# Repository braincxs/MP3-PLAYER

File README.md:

hello, I am Brian (16 years old)

During exam, i keep seeing people using a EXPENSIVE mp3 player around RM200 (50$), and it's not even hard to build so I said why not build one and that's what i did :)
And it was a lot of fun, pcb designing is a MUST TRY

# BITSTREAM
This is a compact pcb for a custom mp3 player
## Features
- A 8Ω, 2W speaker
- A audio jack for wired earphones
- A tft display screen
- a dfplayer mini and a micro sd car to upload your music
- 4 buttons to select your music
- a rotary encoder to adjust the volume
- an arduino nano

## HOW THIS WAS MADE
I used kicad to make this and it was my first time doing so i think it will have some problem but idk :p

## AI DISCLOSURE
I did use some ai to ask about the safety of the project like what type of battery to use and should i add more resistor.

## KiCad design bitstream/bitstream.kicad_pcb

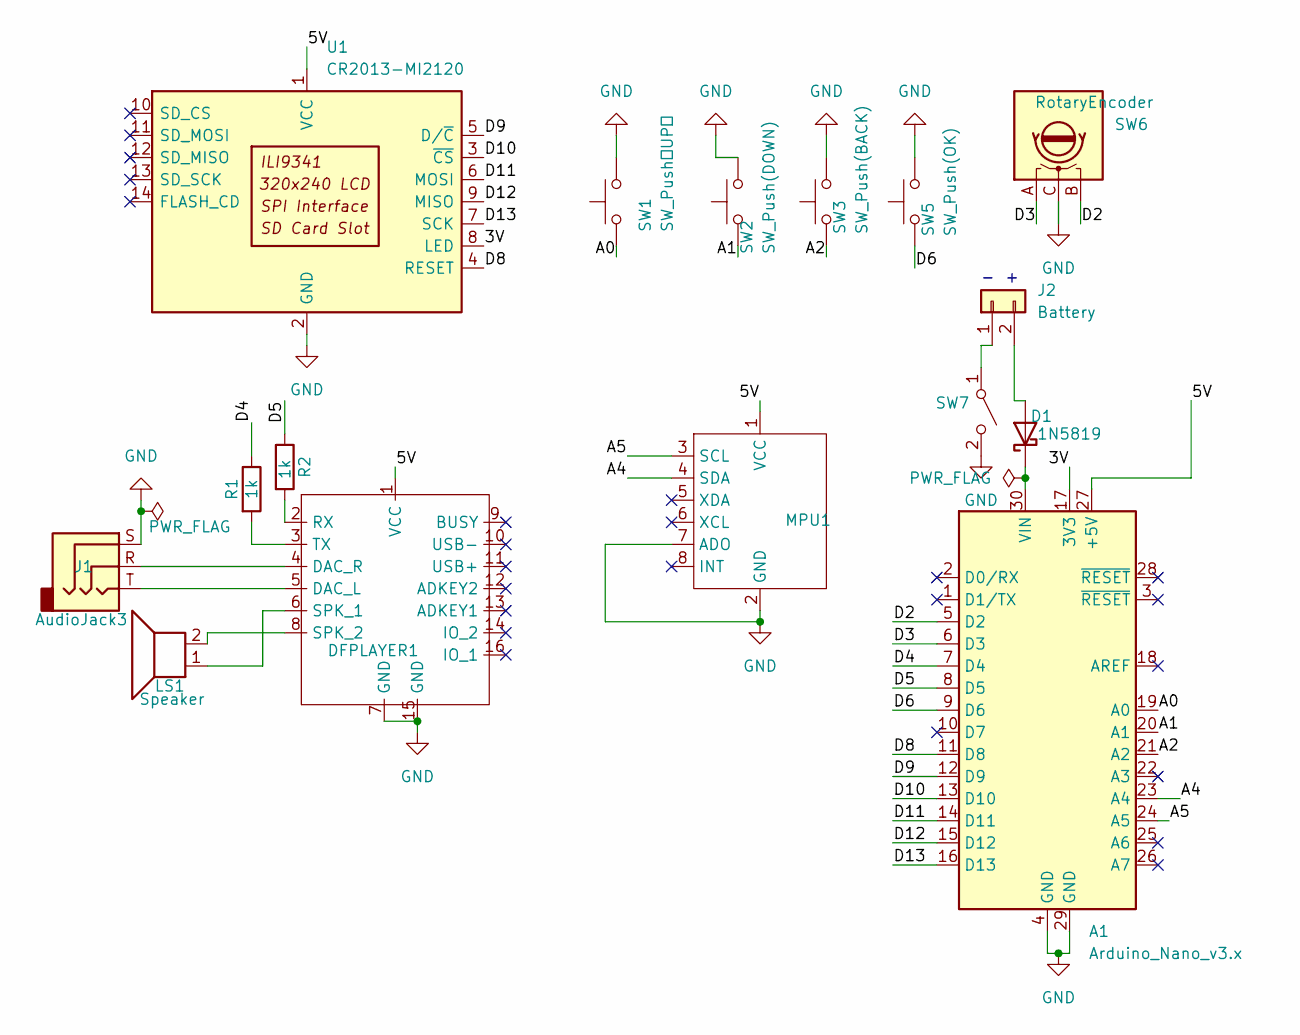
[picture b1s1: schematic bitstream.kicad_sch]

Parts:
A1: Arduino_Nano_v3.x; Arduino_Nano
D1: 1N5819; D_DO-41_SOD81_P10.16mm_Horizontal
DFPLAYER1: dfplayer
J1: AudioJack3; Jack_3.5mm_CUI_SJ-3523-SMT_Horizontal
J2: Battery; TerminalBlock_MaiXu_MX126-5.0-02P_1x02_P5.00mm
LS1: Speaker; SolderWire-0.75sqmm_1x02_P7mm_D1.25mm_OD3.5mm
MPU1: mpu6050
R1, R2: 1k; R_1210_3225Metric_Pad1.30x2.65mm_HandSolder
SW1: SW_Push（UP）; SW_Cherry_MX_1.25u_PCB
SW2: SW_Push(DOWN); SW_Cherry_MX_1.25u_PCB
SW3: SW_Push(BACK); SW_Cherry_MX_1.25u_PCB
SW5: SW_Push(OK); SW_Cherry_MX_1.25u_PCB
SW6: RotaryEncoder; RotaryEncoder_Alps_EC11E-Switch_Vertical_H20mm
SW7: Power switch; SW_Slide_SPDT_Angled_CK_OS102011MA1Q
U1: CR2013-MI2120

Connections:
/3V: A1.17 (3V3), U1.8 (LED)
/5V: A1.27 (+5V), DFPLAYER1.1 (VCC), MPU1.1 (VCC), U1.1 (VCC)
/A0: A1.19 (A0), SW1.1
/A1: A1.20 (A1), SW2.1
/A2: A1.21 (A2), SW3.1
/A4: A1.23 (A4), MPU1.4 (SDA)
/A5: A1.24 (A5), MPU1.3 (SCL)
/D2: A1.5 (D2), SW6.B
/D3: A1.6 (D3), SW6.A
/D4: A1.7 (D4), R1.1
/D5: A1.8 (D5), R2.1
/D6: A1.9 (D6), SW5.1
/D8: A1.11 (D8), U1.4 (RESET)
/D9: A1.12 (D9), U1.5 (D/~C)
/D10: A1.13 (D10), U1.3 (~CS)
/D11: A1.14 (D11), U1.6 (MOSI)
/D12: A1.15 (D12), U1.9 (MISO)
/D13: A1.16 (D13), U1.7 (SCK)
GND: A1.4 (GND), A1.29 (GND), DFPLAYER1.7 (GND), DFPLAYER1.15 (GND), J1.S, MPU1.2 (GND), MPU1.7 (ADO), SW1.2, SW2.2, SW3.2, SW5.2, SW6.C, SW7.2 (B), U1.2 (GND)
unnamed: A1.30 (VIN), D1.1 (K)
unnamed: D1.2 (A), J2.2
unnamed: DFPLAYER1.5 (DAC_L), J1.T
unnamed: DFPLAYER1.4 (DAC_R), J1.R
unnamed: DFPLAYER1.2 (RX), R2.2
unnamed: DFPLAYER1.6 (SPK_1), LS1.1
unnamed: DFPLAYER1.8 (SPK_2), LS1.2
unnamed: DFPLAYER1.3 (TX), R1.2
unnamed: J2.1, SW7.1 (A)

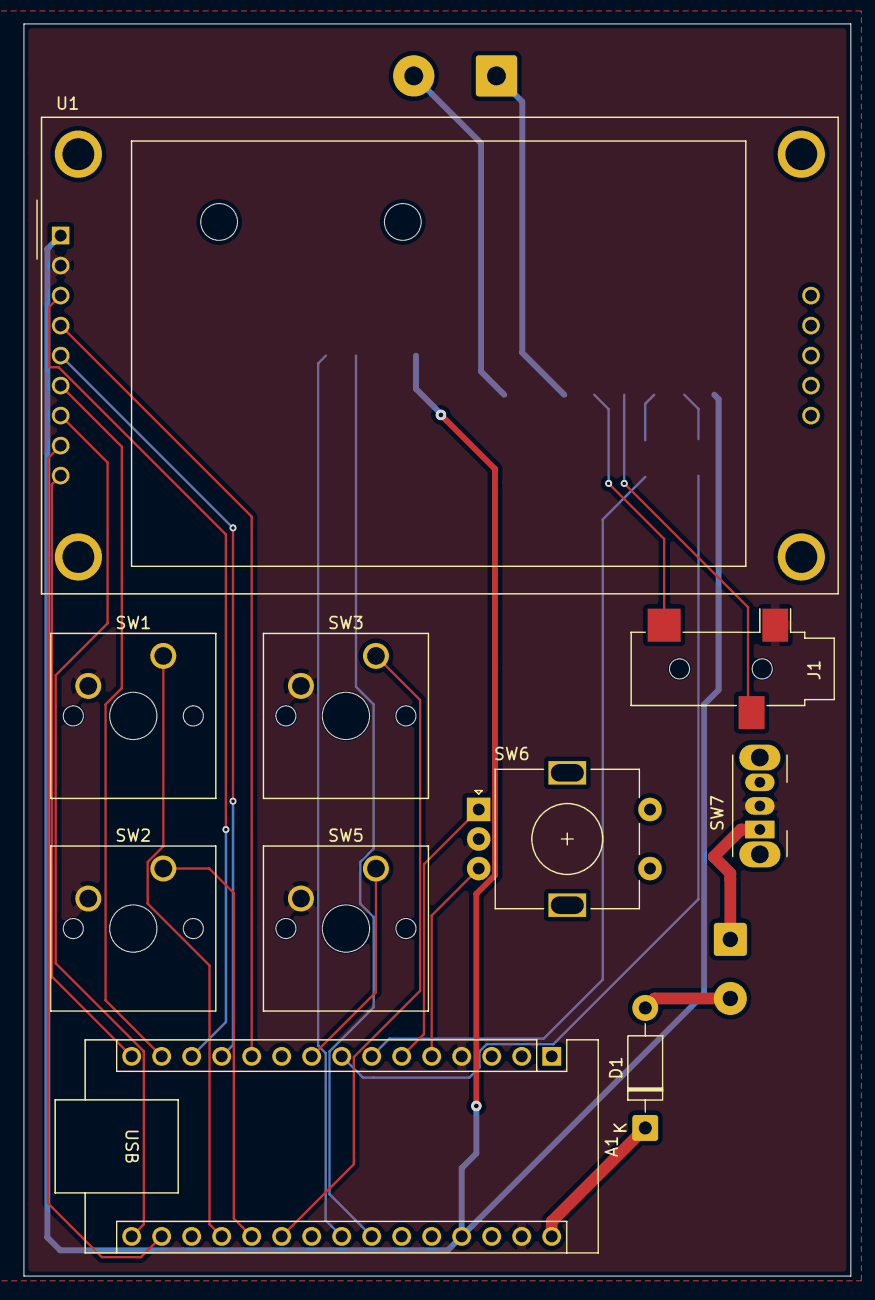
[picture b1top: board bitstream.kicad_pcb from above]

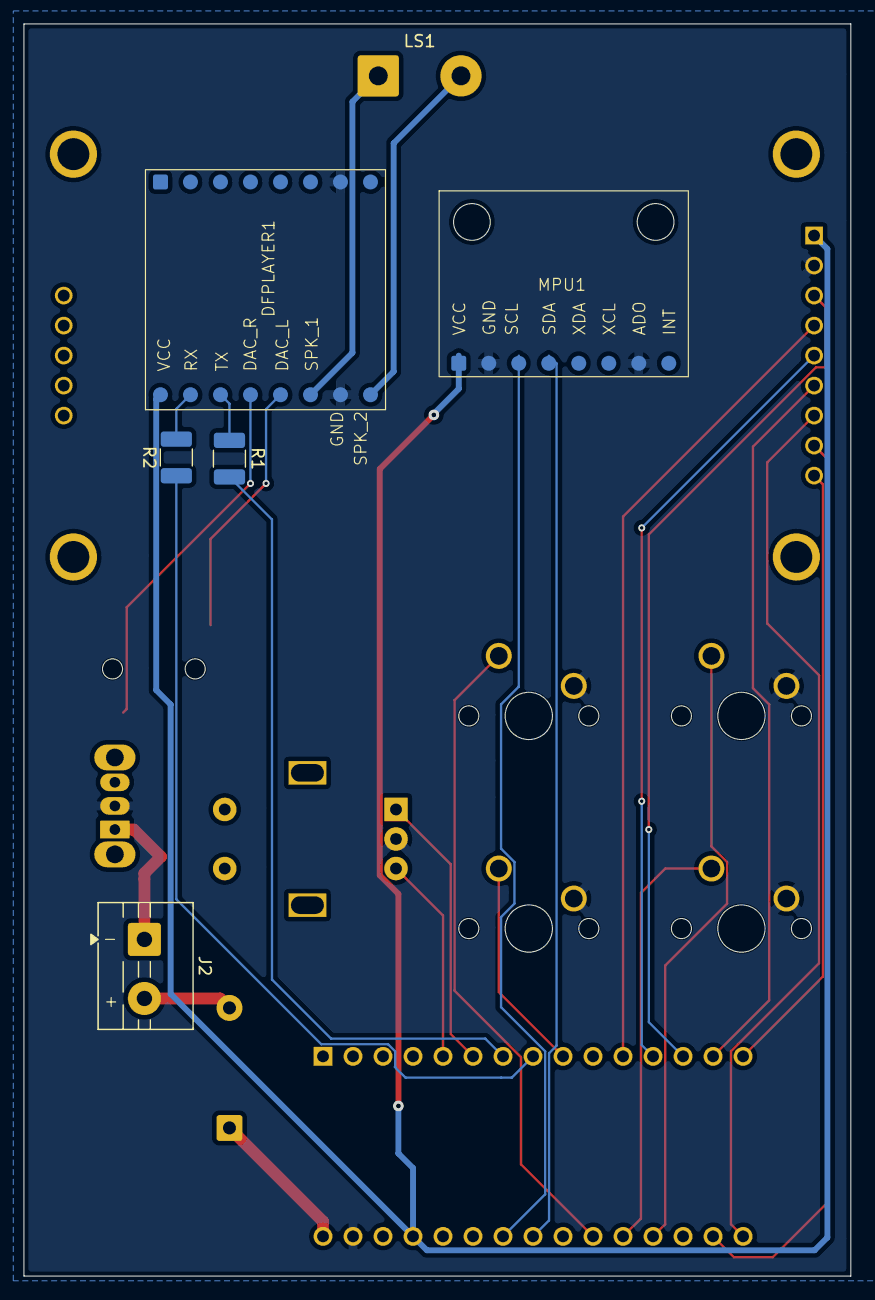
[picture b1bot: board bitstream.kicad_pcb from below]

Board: 4 copper layers, 70.0 x 106.0 mm, 16 parts (6 on the bottom side), 28 nets.
